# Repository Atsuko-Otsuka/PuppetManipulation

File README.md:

# VRぬいぐるみアバター操作システム

ぬいぐるみの身体動作を用いてVR空間のアバターを操作するシステムです。ユーザーがぬいぐるみを「触る」「動かす」ことで、アバターに直感的な身体表現を与えます。全身ボディトラッキングのような装着負担を抑えながら、手軽に自然な操作を実現することを目指しています。

## 概要

### 背景

VR空間におけるアバター操作は普及が進む一方で、従来の手法には次のような課題がありました。

- 全身ボディトラッキングでは、ユーザー自身の身体動作をそのまま反映できる一方で、装着や長時間の運用に伴う身体的負担が大きい
- ボタン式コントローラでは、比較的手軽に操作できる一方で、入力とアバターの動作が一致せず、身体としての直感的な操作が難しい

### 提案

本システムでは、これらの課題を同時に解決するために「ぬいぐるみ」をインターフェースとして採用しました。

ぬいぐるみを用いることで、ユーザーは自然な身体動作をそのままアバター操作に転写できます。これにより、最小限の身体負荷で思い通りの動作を実現しつつ、ユーザーの心理的ハードルを下げることができます。特に、ぬいぐるみを媒介にすることで、キャラクターになりきって大胆で愛らしい動作を自然に引き出すことが可能になります。

## システム構成

### 主要な構成

- 9軸センサ（頭部、両上腕、両前腕、胴体）
- マルチプレクサ（I2C通信）
- XIAO ESP32-C6 マイコン
- Unity ベースのVRアプリケーション
- Meta Quest 3 による視覚提示
- 3Dプリントした筐体とぬいぐるみ内部への搭載

### 通信構成

```
9軸センサ × 7
   ↓ I2C
マルチプレクサ
   ↓ I2C
XIAO ESP32-C6 (マイコン)
   ↓ UDP
PC (Unity)
   ↓
Meta Quest 3 HMD
```

- センサ群は I2C で集約されます
- マイコンがセンサデータを PC に送信します
- PC 上の Unity でアバターの姿勢と動作を更新します
- HMD によってユーザーは VR 空間でアバターを視覚的に確認します

## 使用技術

- Unity（VRアプリケーション開発、アバター制御）
- Arduino IDE / XIAO ESP32-C6（センサデータの取得、PCへのデータ送信）
- KiCad（基板作成）
- Meta Quest 3（ユーザーへの視覚提示）
- Fusion360 / Bamboo Studio（筐体のモデリング、3Dプリンター印刷）

## 通信方式

本システムでは、センサデータを PC へ送信するために UDP 通信を採用しています。

- 通信方式: UDP
- 通信対象: マイコンボード → PC
- 役割: 9軸センサの姿勢情報をリアルタイムに送信し、Unityでアバター制御に反映
- 特徴: 低遅延・ワイヤレス・リアルタイム操作に適している

センサデータはI2Cでマルチプレクサ経由で収集され、ESP32-C6側でパケット化されたのち、Unityへ送信されます。

## ハードウェア詳細

### センサ配置

本システムでは7箇所に9軸センサを配置しています。

- 頭部
- 右上腕
- 右前腕
- 左上腕
- 左前腕
- 胴体
- 追加の計測部位（実装に応じて可変）

### 基板と筐体

- KiCad で設計したセンサ基板を使用
- マルチプレクサにより複数のセンサを一括制御
- 3Dプリントで筐体を作成し、ぬいぐるみの内部へ埋め込み
- ぬいぐるみの内部にセンサユニットを埋め込み、見た目と操作性を両立

### 3Dプリントと製作例

- 基板回路図と基板デザインを作成
- 筐体をプリントして内部に組み込み
- ぬいぐるみ内部へセンサー基板と配線を納めて完成

## システムの流れ

1. ぬいぐるみの各部位で姿勢が変化する
2. 9軸センサがその変化を計測する
3. マルチプレクサを介してマイコンへ送信される
4. XIAO ESP32-C6 が UDP で Unity 側へデータ送信する
5. Unity が受信した姿勢情報をアバターの各部位へ適用する
6. HMD を通じてユーザーは VR 空間で操作結果を確認する

## 実装上のポイント

- センサの取り付け位置は、アバターの自然な動きと操作性を両立するように設計
- ぬいぐるみ内部への埋め込みにより、見た目の違和感を抑制
- アバターの動きは、姿勢角度をそのまま各ボーンへ反映するのではなく、必要に応じて補正や平滑化を行う
- UDP の低遅延性を活かして、VR環境における直感的な操作を優先

## 実装ファイル

このリポジトリには、Unity側の操作スクリプトやシリアル/UDP関連の実装が含まれています。

- Unity アプリケーション: `PuppetManipulation_Software/`
- ハードウェア(基板、Arduino IDE、3Dプリンタデータなど): `PuppetManipulation_Hardware/`
- センサ制御と通信: `Assets/` 配下のスクリプト群
- キャラクター制御: `Assets/Scripts/Puppet/` など

## セットアップ

### 必要な環境

- Unity
- Meta Quest 3
- XIAO ESP32-C6
- Arduino IDE
- KiCad（基板改造時）
- 3Dプリンタ（筐体作成時）

### 基本的な手順

1. このリポジトリをクローンする
2. Unity プロジェクトを開く
3. マイコンにセンサ制御プログラムを書き込む
4. ぬいぐるみにセンサユニットを取り付ける
5. Unity 実行時に UDP 接続を確認する
6. VR 空間でアバターが動くことを確認する

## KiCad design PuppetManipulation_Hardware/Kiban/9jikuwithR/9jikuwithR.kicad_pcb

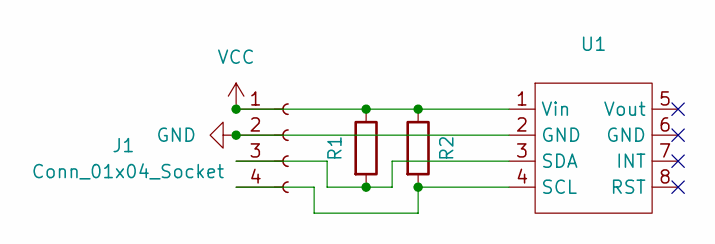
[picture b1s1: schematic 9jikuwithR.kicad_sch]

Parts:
J1: Conn_01x04_Socket; JST_XH_B4B-XH-A_1x04_P2.50mm_Vertical
R1, R2: R; R_Axial_DIN0207_L6.3mm_D2.5mm_P7.62mm_Horizontal
U1: DIP-8_W7.62mm

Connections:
GND: J1.2, U1.2 (GND)
unnamed: J1.3, R1.2, U1.3 (SDA)
unnamed: J1.4, R2.2, U1.4 (SCL)
VCC: J1.1, R1.1, R2.1, U1.1 (Vin)

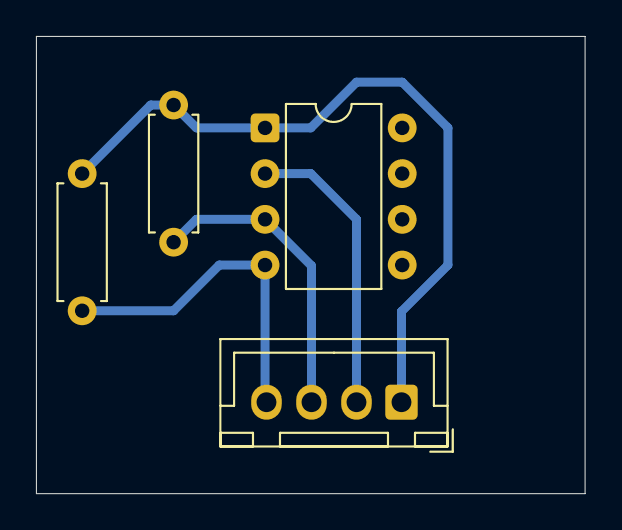
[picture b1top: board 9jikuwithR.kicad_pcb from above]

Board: 2 copper layers, 30.5 x 25.4 mm, 4 parts (0 on the bottom side), 4 nets.

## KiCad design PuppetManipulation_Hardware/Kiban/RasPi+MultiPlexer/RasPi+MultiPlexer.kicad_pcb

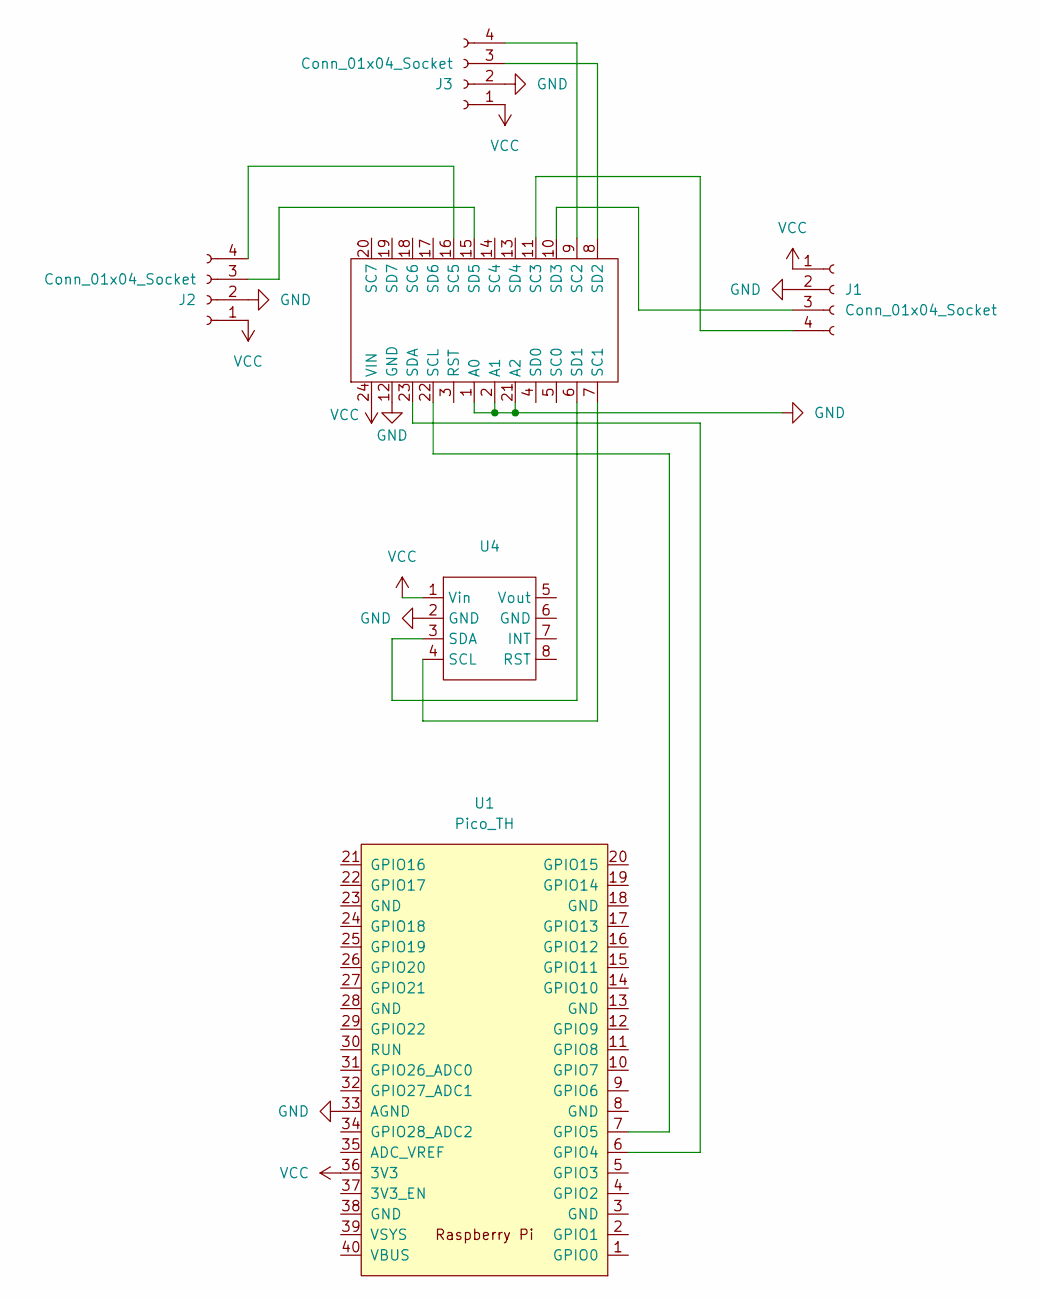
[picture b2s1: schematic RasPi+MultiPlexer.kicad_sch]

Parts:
J1, J2, J3: Conn_01x04_Socket; JST_XH_S4B-XH-A_1x04_P2.50mm_Horizontal
U1: Pico_TH; RPi_Pico_TH
U2: TCA9548A
U4: DIP-8_W7.62mm

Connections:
GND: J1.2, J2.2, J3.2, U1.33 (AGND), U2.1 (A0), U2.2 (A1), U2.12 (GND), U2.21 (A2), U4.2 (GND)
unnamed: J1.3, U2.10 (SD3)
unnamed: J1.4, U2.11 (SC3)
unnamed: J2.3, U2.15 (SD5)
unnamed: J2.4, U2.16 (SC5)
unnamed: J3.3, U2.8 (SD2)
unnamed: J3.4, U2.9 (SC2)
unnamed: U1.6 (GPIO4), U2.23 (SDA)
unnamed: U1.7 (GPIO5), U2.22 (SCL)
unnamed: U2.7 (SC1), U4.4 (SCL)
unnamed: U2.6 (SD1), U4.3 (SDA)
VCC: J1.1, J2.1, J3.1, U1.36 (3V3), U2.24 (VIN), U4.1 (Vin)

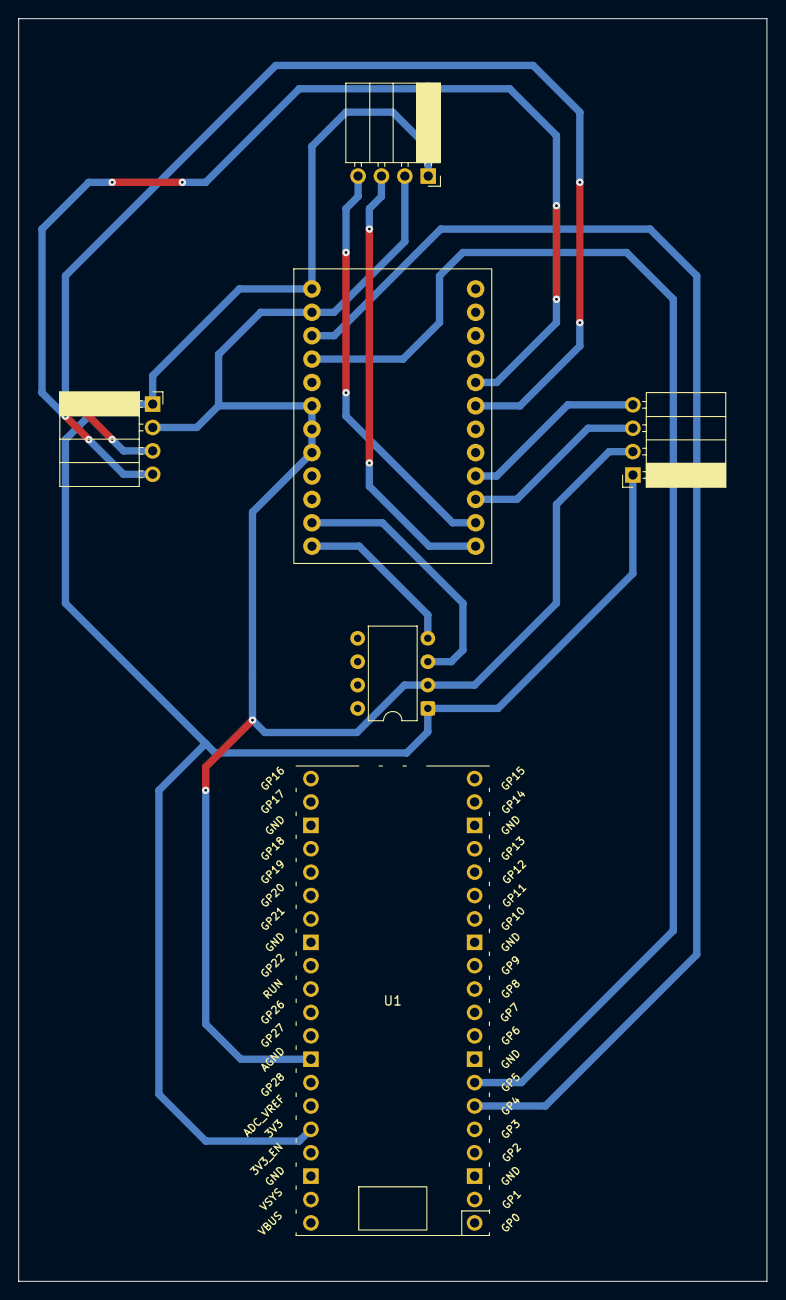
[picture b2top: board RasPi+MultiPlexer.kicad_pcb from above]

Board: 2 copper layers, 81.3 x 137.2 mm, 6 parts (0 on the bottom side), 12 nets.

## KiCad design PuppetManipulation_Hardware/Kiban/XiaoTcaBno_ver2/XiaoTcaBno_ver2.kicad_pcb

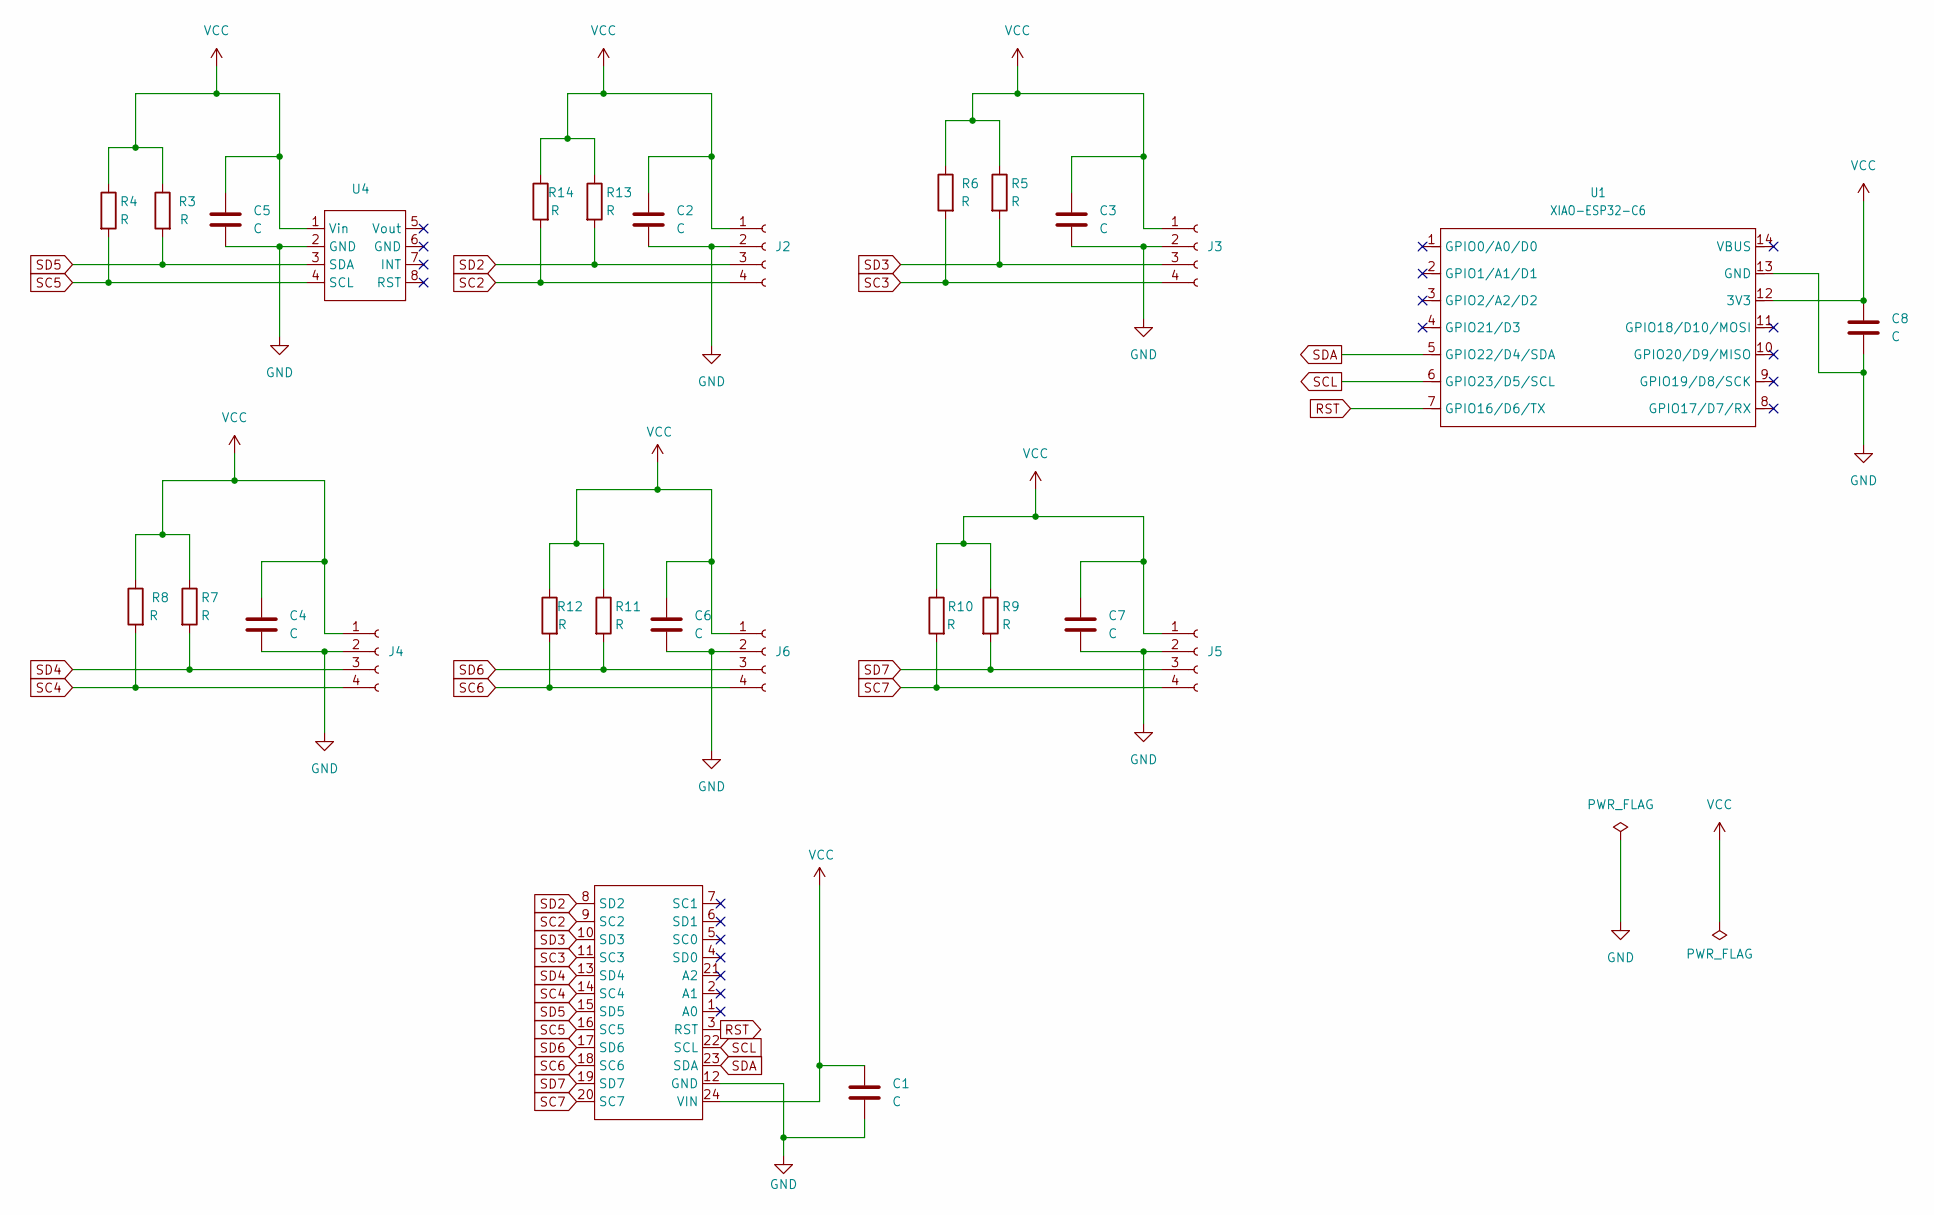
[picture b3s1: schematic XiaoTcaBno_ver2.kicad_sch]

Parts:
C1, C2, C3, C4, C5, C6, C7: C; C_Disc_D3.0mm_W1.6mm_P2.50mm
C8: C; CP_Radial_D6.3mm_P2.50mm
J2, J3, J4, J5, J6: Conn_01x04_Socket; JST_XH_B4B-XH-A_1x04_P2.50mm_Vertical
R3, R4, R5, R6, R7, R8, R9, R10, R11, R12, R13, R14: R; R_Axial_DIN0204_L3.6mm_D1.6mm_P7.62mm_Horizontal
U1: XIAO-ESP32-C6; XIAO-ESP32-C6-DIP
U2: TCA9548A
U4: DIP-8_W7.62mm

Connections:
GND: C1.2, C2.2, C3.2, C4.2, C5.2, C6.2, C7.2, C8.2, J2.2, J3.2, J4.2, J5.2, J6.2, U1.13 (GND), U2.12 (GND), U4.2 (GND)
RST: U1.7 (GPIO16/D6/TX), U2.3 (RST)
SC2: J2.4, R14.2, U2.9 (SC2)
SC3: J3.4, R6.2, U2.11 (SC3)
SC4: J4.4, R8.2, U2.14 (SC4)
SC5: R4.2, U2.16 (SC5), U4.4 (SCL)
SC6: J6.4, R12.2, U2.18 (SC6)
SC7: J5.4, R10.2, U2.20 (SC7)
SCL: U1.6 (GPIO23/D5/SCL), U2.22 (SCL)
SD2: J2.3, R13.2, U2.8 (SD2)
SD3: J3.3, R5.2, U2.10 (SD3)
SD4: J4.3, R7.2, U2.13 (SD4)
SD5: R3.2, U2.15 (SD5), U4.3 (SDA)
SD6: J6.3, R11.2, U2.17 (SD6)
SD7: J5.3, R9.2, U2.19 (SD7)
SDA: U1.5 (GPIO22/D4/SDA), U2.23 (SDA)
VCC: C1.1, C2.1, C3.1, C4.1, C5.1, C6.1, C7.1, C8.1, J2.1, J3.1, J4.1, J5.1, J6.1, R3.1, R4.1, R5.1, R6.1, R7.1, R8.1, R9.1, R10.1, R11.1, R12.1, R13.1, R14.1, U1.12 (3V3), U2.24 (VIN), U4.1 (Vin)

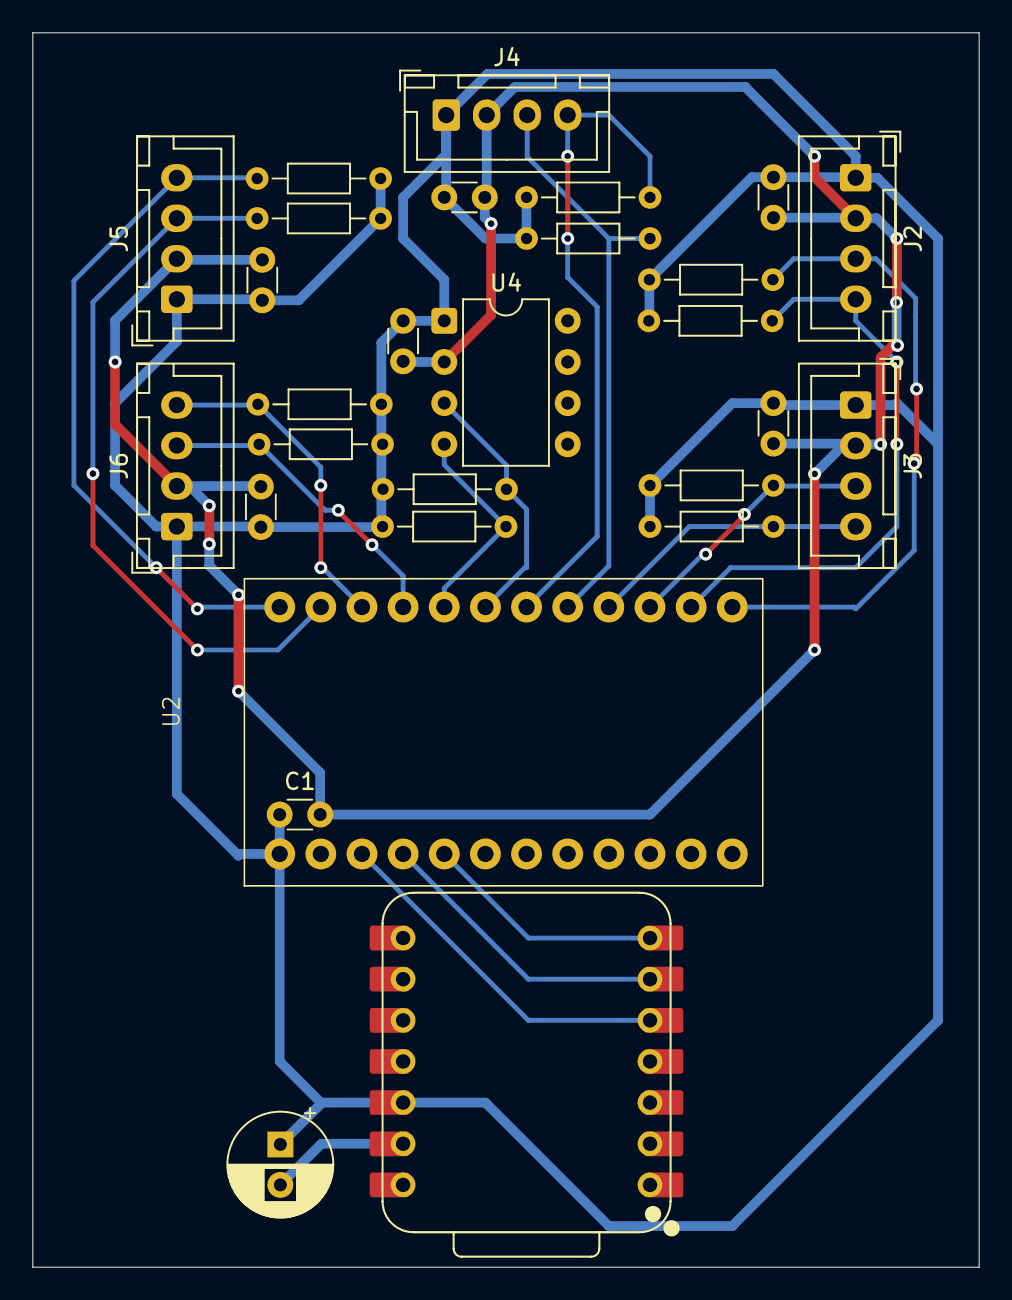
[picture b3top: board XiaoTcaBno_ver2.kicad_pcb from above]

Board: 2 copper layers, 58.4 x 76.2 mm, 28 parts (0 on the bottom side), 17 nets.

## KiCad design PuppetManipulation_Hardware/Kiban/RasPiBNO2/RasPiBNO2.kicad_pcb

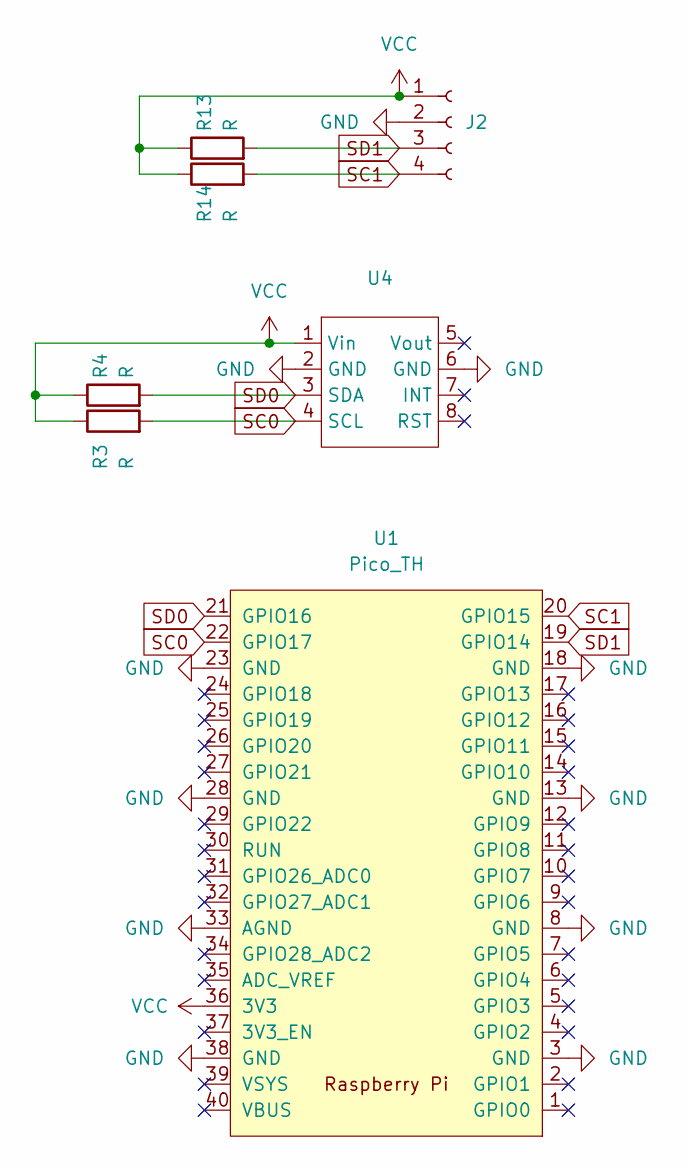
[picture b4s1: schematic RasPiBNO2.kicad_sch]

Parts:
J2: Conn_01x04_Socket; JST_XH_B4B-XH-A_1x04_P2.50mm_Vertical
R3, R4, R13, R14: R; R_Axial_DIN0207_L6.3mm_D2.5mm_P10.16mm_Horizontal
U1: Pico_TH; RPi_Pico_TH
U4: DIP-8_W7.62mm

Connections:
GND: J2.2, U1.3 (GND), U1.8 (GND), U1.13 (GND), U1.18 (GND), U1.23 (GND), U1.28 (GND), U1.33 (AGND), U1.38 (GND), U4.2 (GND), U4.6 (GND)
SC0: R3.2, U1.22 (GPIO17), U4.4 (SCL)
SC1: J2.4, R14.2, U1.20 (GPIO15)
SD0: R4.2, U1.21 (GPIO16), U4.3 (SDA)
SD1: J2.3, R13.2, U1.19 (GPIO14)
VCC: J2.1, R3.1, R4.1, R13.1, R14.1, U1.36 (3V3), U4.1 (Vin)

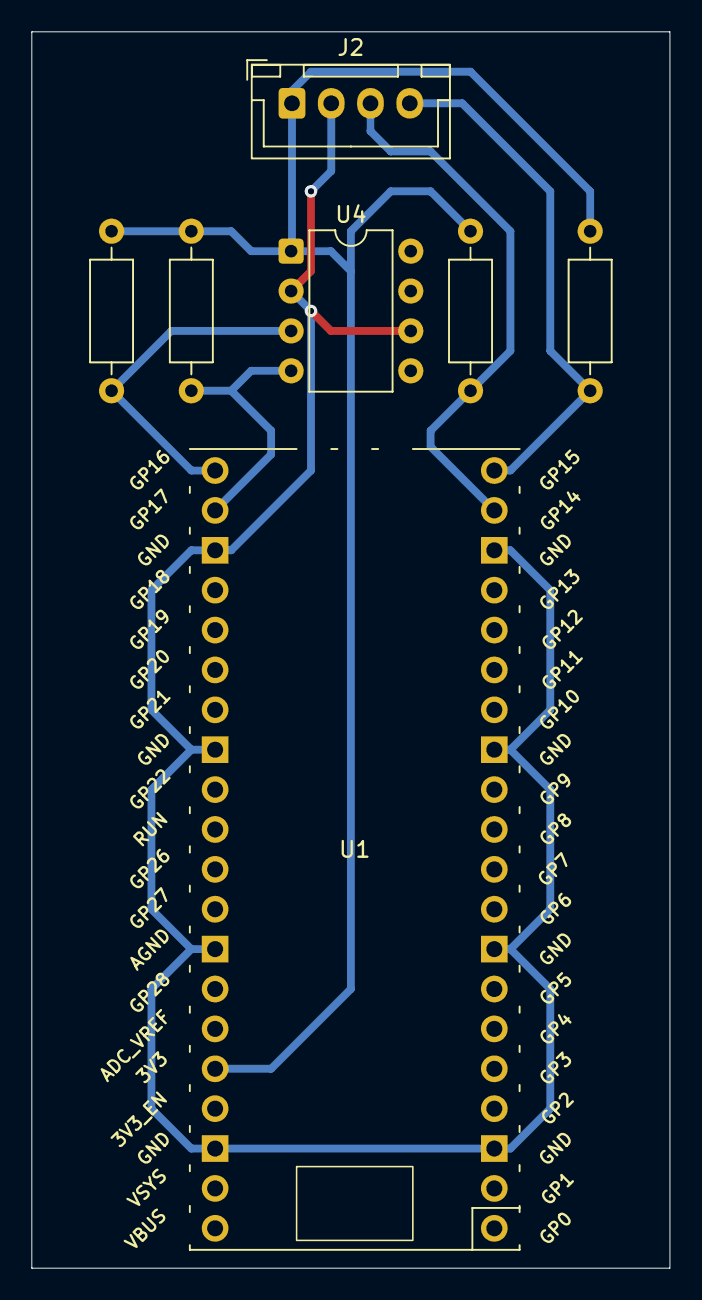
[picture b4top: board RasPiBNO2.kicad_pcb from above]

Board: 2 copper layers, 40.6 x 78.7 mm, 7 parts (0 on the bottom side), 6 nets.

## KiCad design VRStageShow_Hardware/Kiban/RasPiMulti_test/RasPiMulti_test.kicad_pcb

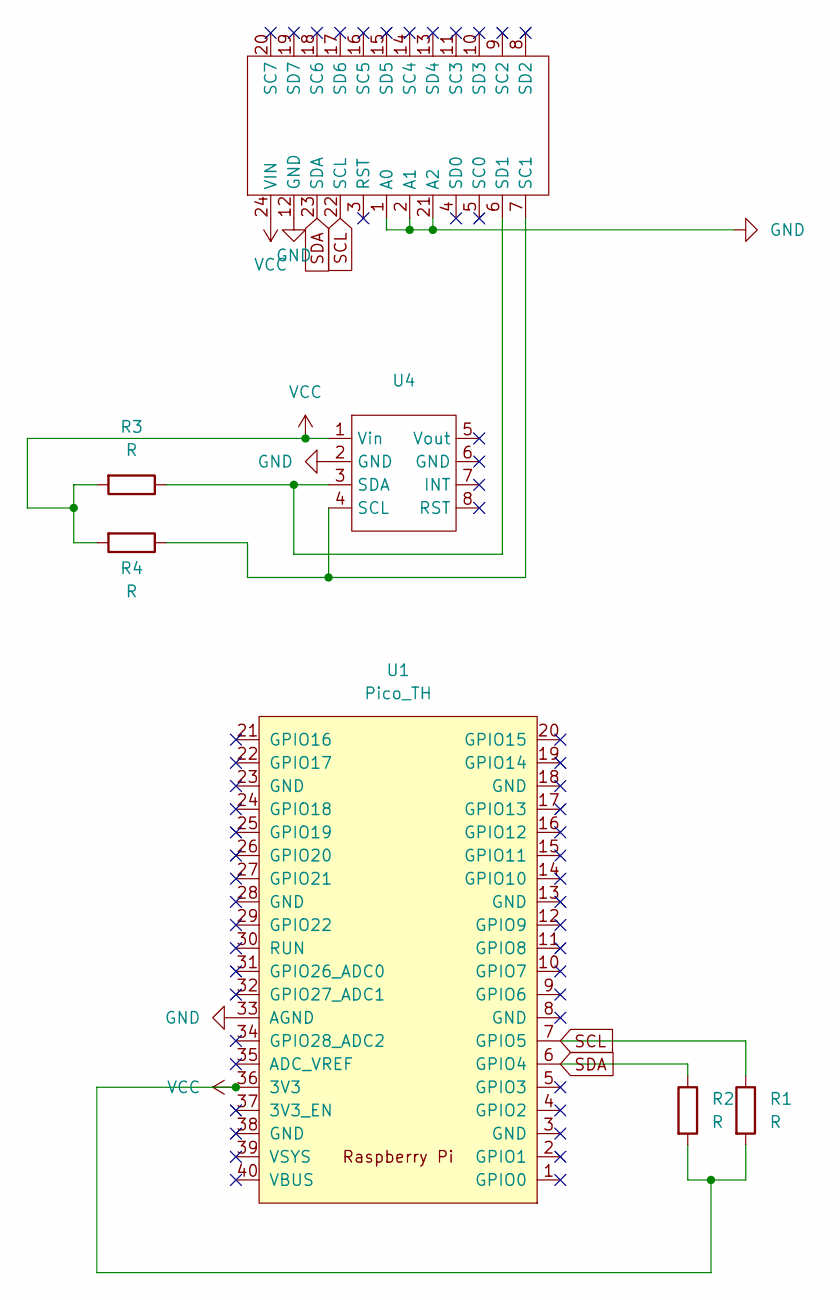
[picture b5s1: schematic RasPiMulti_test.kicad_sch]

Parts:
R1, R2, R3, R4: R; R_Axial_DIN0204_L3.6mm_D1.6mm_P7.62mm_Horizontal
U1: Pico_TH; RPi_Pico_TH
U2: TCA9548A
U4: DIP-8_W7.62mm

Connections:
GND: U1.33 (AGND), U2.1 (A0), U2.2 (A1), U2.12 (GND), U2.21 (A2), U4.2 (GND)
unnamed: R4.1, U2.7 (SC1), U4.4 (SCL)
unnamed: R3.1, U2.6 (SD1), U4.3 (SDA)
SCL: R1.1, U1.7 (GPIO5), U2.22 (SCL)
SDA: R2.1, U1.6 (GPIO4), U2.23 (SDA)
VCC: R1.2, R2.2, R3.2, R4.2, U1.36 (3V3), U2.24 (VIN), U4.1 (Vin)

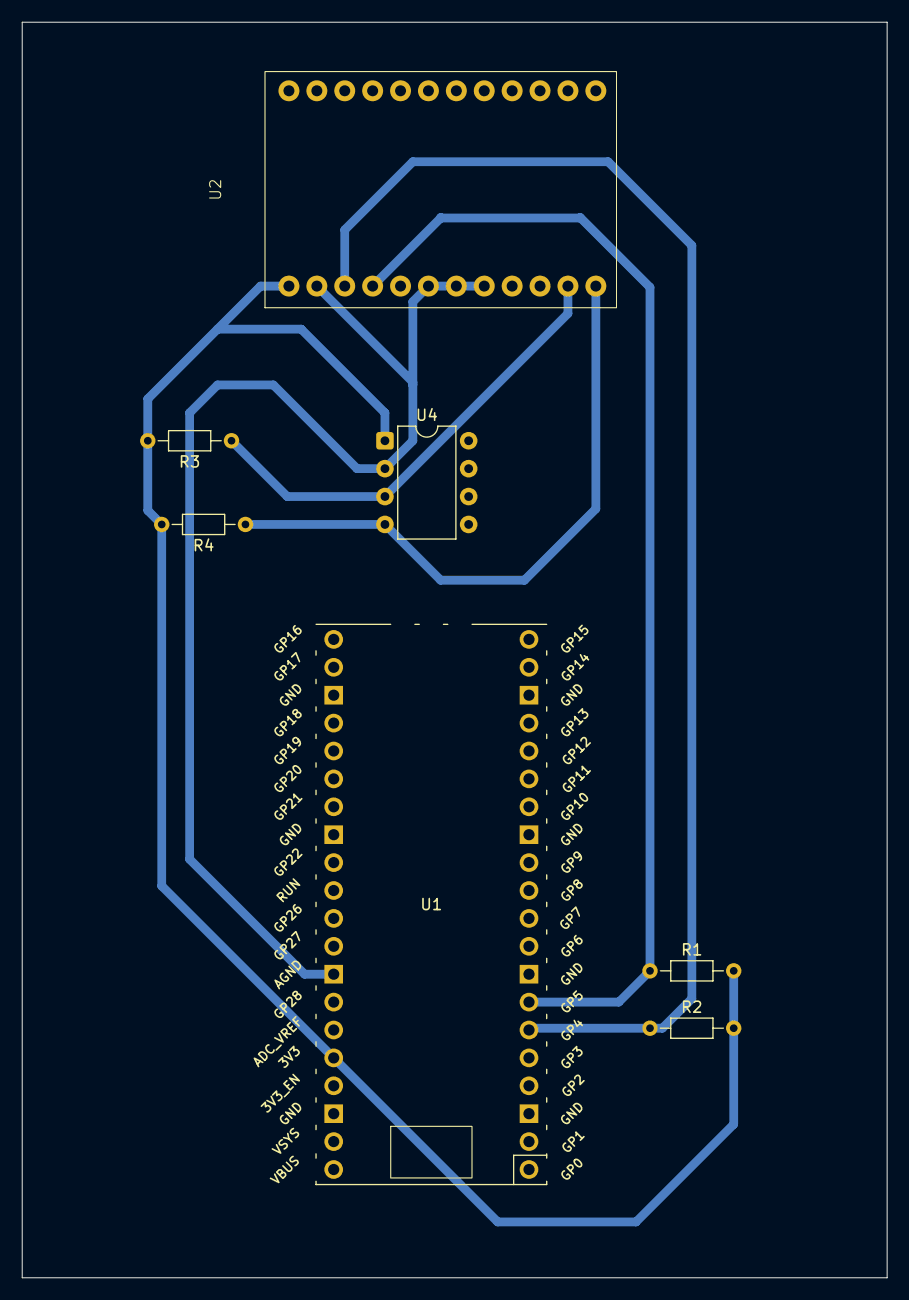
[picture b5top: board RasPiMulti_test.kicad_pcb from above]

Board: 2 copper layers, 78.7 x 114.3 mm, 7 parts (0 on the bottom side), 6 nets.

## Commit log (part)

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2026-04-27 upload
2026-04-30 edit name
2026-05-08 edit posemagic scene
2026-05-08 edit posemagic scene powerup commnd
2026-05-13 reload
2026-06-17 Make and Edit Application Scene
